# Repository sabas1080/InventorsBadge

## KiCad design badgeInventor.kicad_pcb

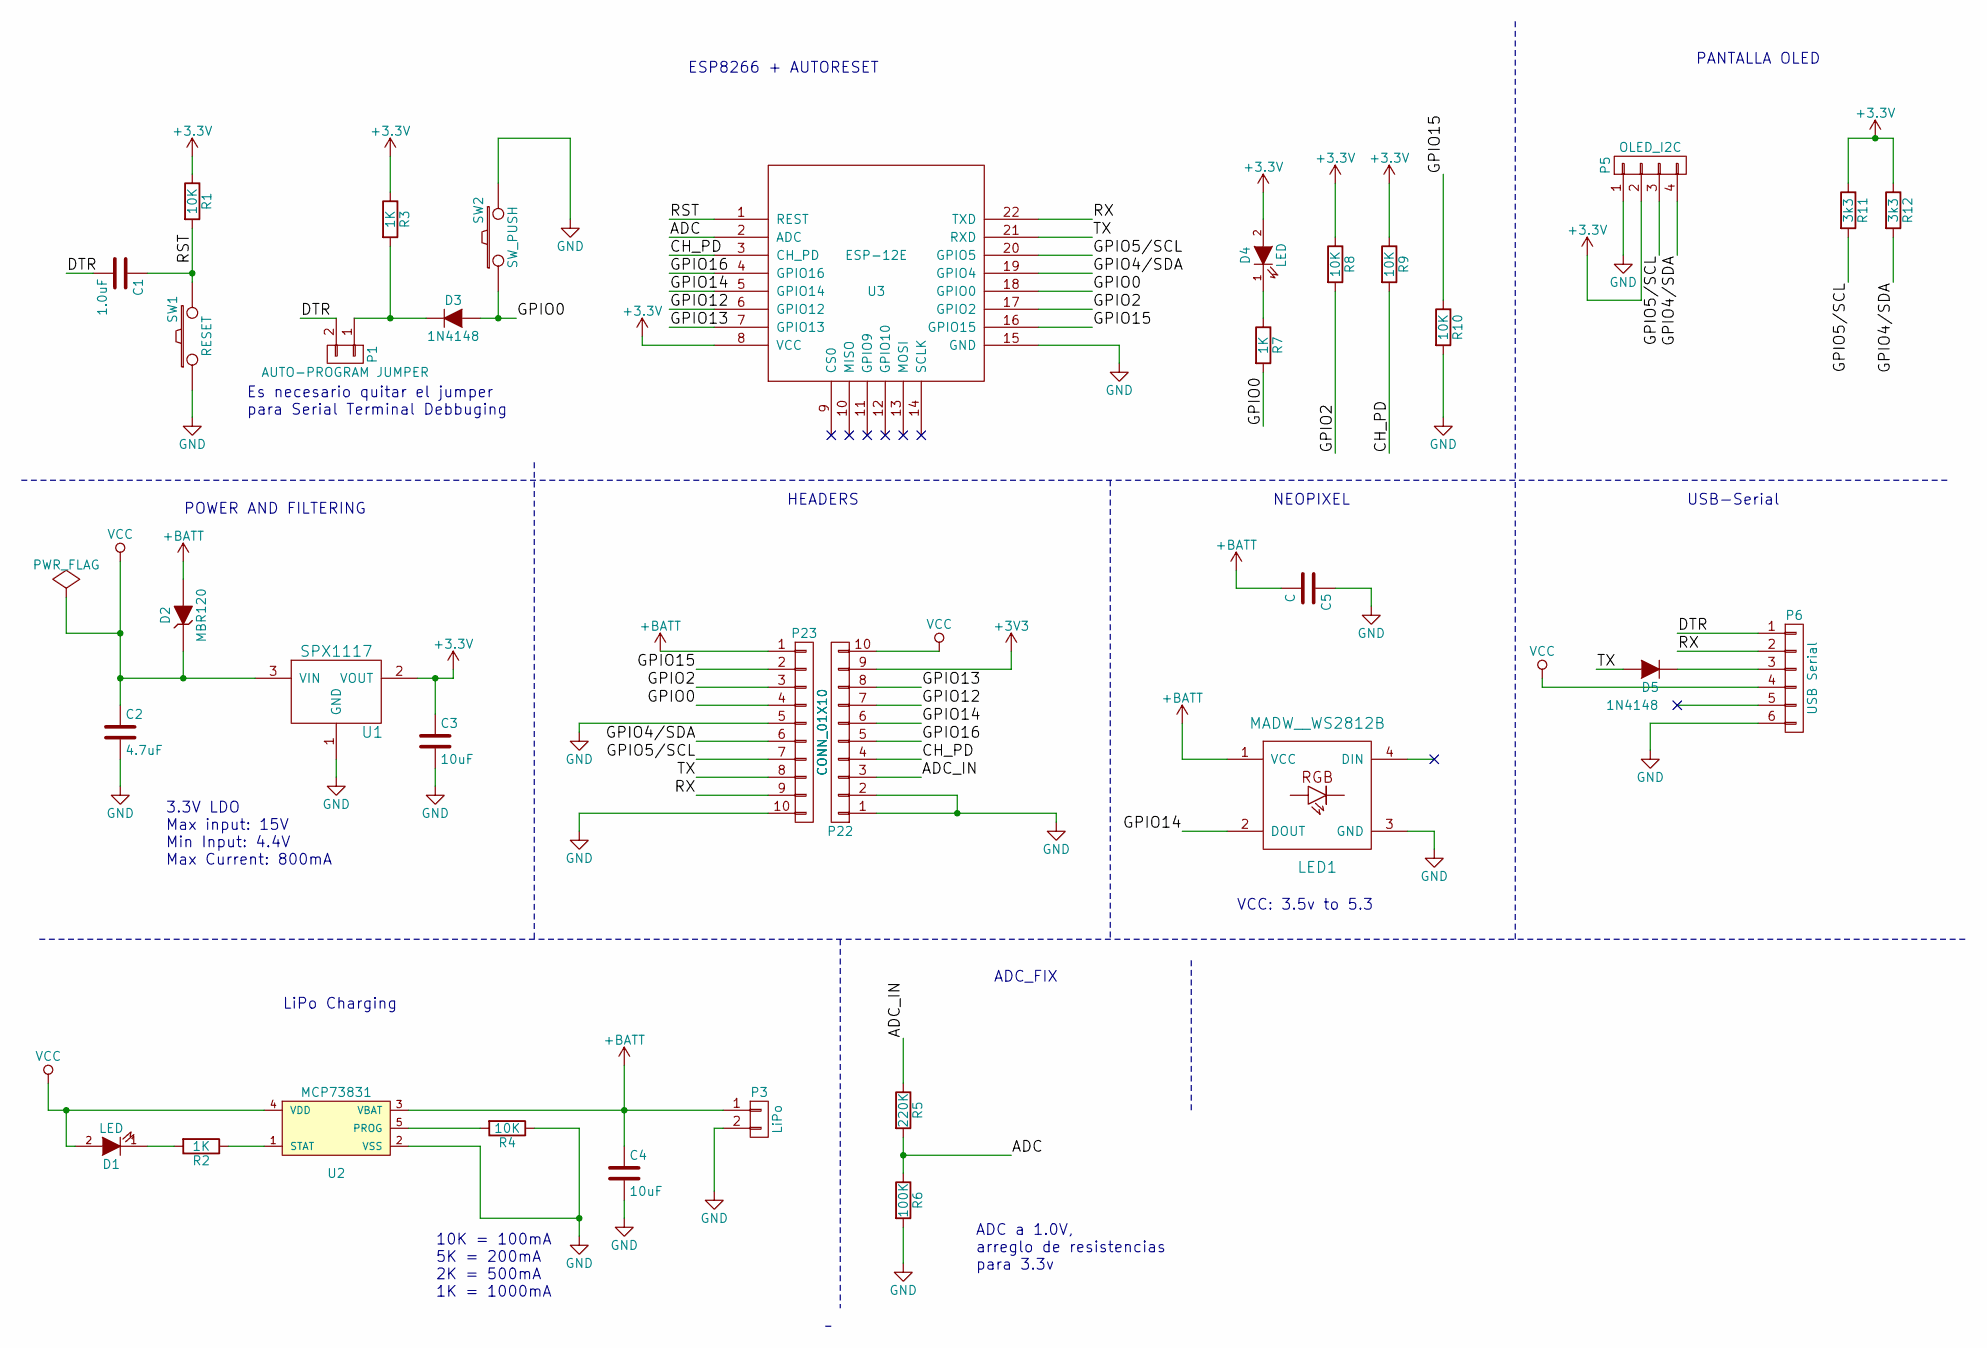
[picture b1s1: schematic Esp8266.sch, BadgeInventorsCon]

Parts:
C1: 1.0uF; C_0805_HandSoldering
C2: 4.7uF; C_0805_HandSoldering
C3, C4: 10uF; C_0805_HandSoldering
C5: C; C_0805_HandSoldering
D1: LED; LED-0603
D2: MBR120; SOD-123
D3, D5: 1N4148; SOD-323
D4: LED; LED-0805
LED1: MADW__WS2812B; WS2812B_PP
P1: AUTO-PROGRAM JUMPER; Pin_Header_Straight_1x02
P3: LiPo; CONN_JST-2_SMD
P5: OLED_I2C; Socket_Strip_Straight_1x04
P6: USB Serial; Socket_Strip_Straight_1x06
P22, P23: CONN_01X10; Pin_Header_Straight_1x10
R1, R4, R8, R9, R10: 10K; R_0805_HandSoldering
R2, R3, R7: 1K; R_0805_HandSoldering
R5: 220K; R_0805_HandSoldering
R6: 100K; R_0805_HandSoldering
R11, R12: 3k3; R_0805_HandSoldering
SW1: RESET; SW_PUSH_SMD
SW2: SW_PUSH; SW_PUSH_SMD
U1: SPX1117; SOT-223
U2: MCP73831; SOT-23-5
U3: ESP-12E

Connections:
+BATT: C4.1, C5.2, D2.2 (A), LED1.1 (VCC), P3.1, P23.1, U2.3 (VBAT); also elsewhere on the board
/ESP8266/ADC: R5.2, R6.1, U3.2 (ADC)
/ESP8266/ADC_IN: P22.3, R5.1
/ESP8266/CH_PD: P22.4, R9.2, U3.3 (CH_PD)
/ESP8266/DTR: C1.2, P1.2, P6.1
/ESP8266/GPIO0: D3.2 (A), P23.4, R7.2, SW2.1, U3.18 (GPIO0)
/ESP8266/GPIO2: P23.3, R8.2, U3.17 (GPIO2)
/ESP8266/GPIO4/SDA: P5.4, P23.6, R12.2, U3.19 (GPIO4)
/ESP8266/GPIO5/SCL: P5.3, P23.7, R11.2, U3.20 (GPIO5)
/ESP8266/GPIO12: P22.7, U3.6 (GPIO12); also elsewhere on the board
/ESP8266/GPIO13: P22.8, U3.7 (GPIO13)
/ESP8266/GPIO14: LED1.2 (DOUT), P22.6, U3.5 (GPIO14)
/ESP8266/GPIO15: P23.2, R10.1, U3.16 (GPIO15)
/ESP8266/GPIO16: P22.5, U3.4 (GPIO16)
/ESP8266/RST: C1.1, R1.2, SW1.2, U3.1 (REST)
/ESP8266/RX: P6.2, P23.9, U3.22 (TXD)
/ESP8266/TX: D5.2 (A), P23.8, U3.21 (RXD)
GND: C2.2, C3.2, C4.2, C5.1, LED1.3 (GND), P3.2, P5.1, P6.6, P22.1, P22.2, P23.5, P23.10, R4.1, R6.2, R10.2, SW1.1, SW2.2, U1.1 (GND), U2.2 (VSS), U3.15 (GND)
unnamed: D1.1 (K), R2.2
unnamed: D3.1 (K), P1.1, R3.2
unnamed: D4.1 (K), R7.1
unnamed: D5.1 (K), P6.3
unnamed: R2.1, U2.1 (STAT)
unnamed: R4.2, U2.5 (PROG)
VCC: C2.1, D1.2 (A), D2.1 (K), P6.4, P22.10, U1.3 (VIN), U2.4 (VDD)

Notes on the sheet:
10K = 100mA 5K = 200mA 2K = 500mA 1K = 1000mA
LiPo Charging
POWER AND FILTERING
ESP8266 + AUTORESET
PANTALLA OLED
Es necesario quitar el jumper para Serial Terminal Debbuging
NEOPIXEL
USB-Serial
HEADERS
ADC_FIX
ADC a 1.0V, arreglo de resistencias para 3.3v
3.3V LDO Max input: 15V Min Input: 4.4V Max Current: 800mA
VCC: 3.5v to 5.3

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
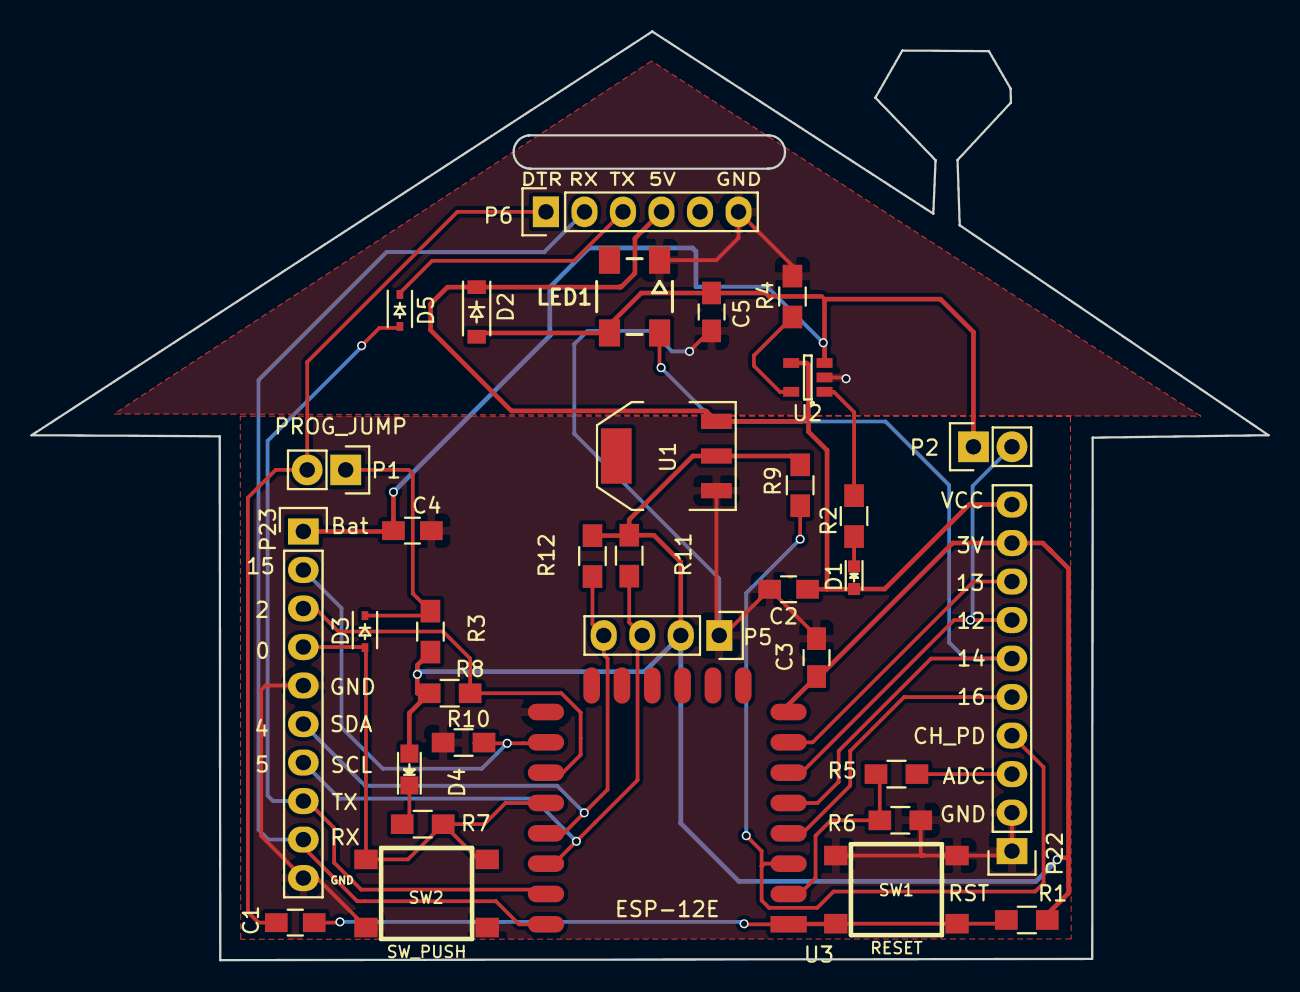
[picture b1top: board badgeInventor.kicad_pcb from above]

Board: 2 copper layers, 81.6 x 61.3 mm, 35 parts (1 on the bottom side), 26 nets.

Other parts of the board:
P2: CONN_01X10; Pin_Header_Straight_1x02

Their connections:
+BATT: P2.1; also elsewhere on the board
/ESP8266/GPIO12: P2.2; also elsewhere on the board

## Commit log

2015-12-12 Version 006
2015-12-13 Version 006-071215
2015-12-13 Version 007-121215
2015-12-17 Cambio circuito, inicio PCB
2015-12-17 Add footprint inventor
2015-12-18 PCB v0.01
2015-12-18 Edge Cut
2015-12-19 Agregado EdgeCut, reacomodo de etiquetas y nombre de Serial
2015-12-19 Agregado pinout, correccion diodo TX
2015-12-21 Names
2016-02-20 News
2016-02-20 Agregado logos y para colgar
